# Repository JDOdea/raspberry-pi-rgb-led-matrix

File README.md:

Controlling RGB LED display with Raspberry Pi GPIO
==================================================

A recreated and modified library for controlling 64x64, 32x32, or 16x32 RGB LED panels using a Raspberry Pi. Can support PWM up to 11Bit per channel, providing true 24bpp color with CIE1931 profile.
Original repo can be found [here](https://github.com/hzeller/rpi-rgb-led-matrix).

Supports 3 chains with many panels each on a regular Pi, as per the original repo's README.
Raspberry Pi 2 or 3 can chain 12 panels in that chain (36 panels total), with 96-ish panels (32 chain length) being potentially possible.
Fewer colors or so-called 'outdoor panels' can control even more, faster.

Overview
--------
The RGB LED matrix panels can be bought at [Sparkfun][sparkfun], [AdaFruit][ada] or eBay and Aliexpress. If located in China, try to get directly from some manufacturer, Taobao or Alibaba.

The `RGBMatrix` class in `include/led-matrix.h` is what controls these.
Go to [utils/directory for some ready-made tools](./utils) to get started using the library, or the [examples-api-use/](./examples-api-use/) directory if you want to get started programming your own utils.

Raspberry Pi up to 4 supported
------------------------------

This library supports the old Raspberry Pi's Version 1 with 26 pin header and also the B+ models, the Pi Zero, Raspberry Pi 2 and 3 with 40 pins, as well as the Compute Modules which have 44 GPIOs.

The Raspberry Pi 5 still needs some research into the vastly changed peripherals and is not yet supported. See https://github.com/hzeller/rpi-rgb-led-matrix/issues/1603#issuecomment-2624713250 and https://github.com/adafruit/Adafruit_Blinka_Raspberry_Pi5_Piomatter

The 26 pin models can drive one chain of RGB panels, the 40 pin models **up to three** chains in parallel (each chain 12 or more panels long). The Compute Module can drive **up to 6 chains in parallel**. The Raspberry Pi 2 and 3 are faster and generally preferred to the older models (and the Pi Zero). With the faster models, the panels sometimes can't keep up with the speed; check out this [troubleshooting section](#troubleshooting) for what to do.

A lightweight, non-GUI, distribution such as [DietPi] is recommended. [Raspbian Lite][raspbian-lite] is a bit easier to get started with and is a good second choice.

Types of Displays
-----------------
There are various types of displays that come all with the same Hub75 connector. They vary in the way the multiplexing is happening so this library supports options to choose that.
All these are configured by flags (or, programmatically, in an [Options struct](include/led-matrix.h#L57)).

If you have a 64x32 display, you need to supply the flags `--led-cols=64 --led-rows=32` for instance.

Depending on the Matrix, there are various configuration options that you might need to set for it to work. See further below in the README for the [detailed description of these](#changing-parameters-via-command-line-flags). While the `--led-rows` and the `--led-cols` can be derived from simply looking at the panels, the other options might require some experimenting to find the right setting if there is no description provided by the manufacturer of the panel. Going through these options for experiments would typically not do harm, so feel free to experiment to find your setting.

Flag                                | Description
:---------------      | :-----------------
`--led-cols`          | Columns in the LED matrix, the 'width'.
`--led-rows`          | Rows in the LED matrix, the 'height'.
`--led-multiplexing`  | In particular bright outdoor panels with small multiplex ratios require this. Often an indicator: if there are fewer address lines than expected: ABC (instead of ABCD) for 32 high panels and ABCD (instead of ABCDE) for 64 high panels.
`--led-row-addr-type` | Adressing of rows; in particular panels with only AB address lines might indicate that this is needed.
`--led-panel-type`    | Chipset of the panel. In particular if it doesn't light up at all, you might need to play with this option because it indicates that the panel requires a particular initialization sequence.

Panels can be chained by connecting the output of one panel to the input of the next panel. You can chain quite a few together, but the refresh rate will reduce with longer chains.

The 64x64 matrixes typically come in two kinds: with 5 address lines (A, B, C, D, E), or (A, B); the latter needs a `--led-row-addr-type=1` parameter. So-called 'outdoor panels' are typically brighter and allow for faster refresh-rate for the same size, but do some multiplexing internally of which there are a few types out there; they can be chosen with the `--led-multiplexing` parameter.

There are some panels that have a different chip-set that the default HUB75. These require some initialization sequence. The current supported types are `--led-panel-type=FM6126A` and `--led-panel-type=FM6127`.
Generally, the higher scan-rate (e.g.1:8), a.k.a. outdoor panels generally allow faster refresh rate, but you might need to figure out the multiplexing mapping if one of the three provided does not work.

Some 32x16 outdoor matrixes with 1:4 scan(e.g. [Quangli Q10(1/4) or X10(1/4)](http://qiangliled.com/products-63.html)) have 4 address line (A, B, C, D). For such matrices is necessary to use the `--led-row-addr-type=2` parameter. Also the matrix Quangli Q10(1/4) has "Z"-stripe pixel mapping and in this case, you'd use two parameters at the same time: `--led-row-addr-type=2 --led-multiplexing=4`.

------------
This documentation is split into parts that help you through the process:

    1. [**Wire up the matrix to your Pi**](./wiring.md). This document describes what goes where. You might also be interested in [breakout boards](./adapter) for that. If you have an [Adafruit HAT] or [Adafruit Bonnet], you can choose that with a command line option [described below](#if-you-have-an-adafruit-hat-or-bonnet)
    2. Run a demo. You find that in the [examples-api-use/](./examples-api-use/#running-some-demos) directory:
```
make -C examples-api-use
sudo examples-api-use/demo -D0
```
    3. Use the utilities. The [utils](./utils/) directory has some ready-made useful utilities to show content. [Go there](./utils/) to see how to compile and run these.
    4. Write your own proframs using the Matrix in C++ or one of the bindings such as Python or C#.

### Wiring / Boards

Please see the [Adapter Boards or Self Wiring](./adapter).

Summary:
- Yes you can self wire without level shifters and it will work most of the time, but if you're not in a hurry, get a board
- [This article](https://www.electrodragon.com/product/rgb-matrix-panel-drive-board-for-raspberry-pi-v2/) **is the recommended solution with 3 channels and level shifters.** You can't go wrong there, but expect a bit of shipping time.
- If shipping time is crucial and you don't want to wire your own, Adafruit sells a single channel board (the electrodragon one is 3 channels), but note that its wiring is non-standard and requires a special compile option or command line argument: https://www.adafruit.com/product/3211

### Utilities

The [utils directory](./utils/) is meant for ready utilities to show images or animated gifs or videos. Read the [README](./utils/README.md) for instructions how to compile.

### API

The library comes as an API that you can use for your own utilities and use-cases.

    * The native library is a C++ library (see [include/](./include/)). Example uses you find in the [examples-api-use/](./examples-api-use/) directory.
    * If you prefer to program in C, there is also a [C API](./include/led-matrix-c.h).
    * In the [python](./bindings/python) subdirectory, you'll find a Python API including a couple of [examples](./bindings/python/samples) to get started.

### Changing parameters via command-line flags

For the programs in this distribution and also automatically in your programs using this library, there are a lot of parameters provided as command line flags so that you don't have to re-compile your programs to tweak them. Some might need to be changed for your particular kind of panel.

Here is a small run-down of what these command-line flags do and when you'd like to change them.

First: if you have a different wiring than described in [wiring](./wiring.md), for instance if you have an Adafruit HAT/Bonnet, you can choose these here:

```
--led-gpio-mapping=<gpio-mapping>: Name of GPIO mapping used. Default "regular"
```

This can have values such as
    - `--led-gpio-mapping=regular`          The standard mapping of this library, described in the [wiring](./wiring.md) page.
    - `--led-gpio-mapping=adafruit-hat`     The Adafruit HAT/Bonnet that uses this library, or
    - `--led-gpio-mapping=adafruit-hat-pwm` Adafruit HAT with the anti-flicker hardware mod [described below](#improving-flicker).
    - `--led-gpio-mapping=compute-module`   Additional 3 parallel chains can be used with the Compute Module.

Learn more about the mappings in the [wiring documentation](wiring.md#alternative-hardware-mappings).

#### GPIO speed

```
--led-slowdown-gpio=<0..4>: Slowdown GPIO. Needed for faster Pis and/or slower panels (Default: 1).
```

The Raspberry Pi starting with Pi2 are putting out data too fast for almost all LED panels seen. In this case, you want to slow down writing to GPIO. Zero for this parameter means 'no slowdown'.

The default 1 (one) typically works fine, but often you have to go even further by setting it to 2 (two). If you have a Raspberry Pi with a slower processor (Model A, A+, B+, Zero), then a value of 0 (zero) might work and is desirable.

A Raspberry Pi 3 or Pi4 might even need higher values for the panels to be happy.

#### Panel Connection
The next most important flags describe the type and number of displays connected:

```
--led-rows=<rows>           : Panel rows. Typically 8, 16, 32, or 64. (Default: 32).
--led-cols=<cols>           : Panel columns. Typically 32 or 64. (Default: 32).
--led-chain=<chained>       : Number of daisy-chained panels. (Default: 1).
--led-parallel=<parallel>   : For A/B+ models of RPi2,3b: parallel chains. range=1..3 (Default: 1, 6 for Compute Module).
```

These are the most important ones: here you choose how many panels you have connected and how many rows are in each panel. Panels can be chained (each panel has an input and output connector, see the [wiring documentation](wiring.md#chains)) -- the `--led-chain` flag tells the library how many panels are chained together. The newer Raspberry Pis allow to connect multiple chains in parallel, the `--led-parallel` flag tells it how many there are.

This illustrates what each of these parameters mean:

##### Panel Type

Typically, panels should just work out of the box, but some panels use a different chip-set that requires some initialization. If you don't see any output on your panel, try setting:

```
--led-panel-type=FM6126A
```

Some panels have the FM6127 chip, which is also an option.

##### Multiplexing
If you have some 'outdoor' panels or panels with different multiplexing, the following will be useful:

```
--led-multiplexing=<0..17> : Mux type: 0=direct; 1=Stripe; 2=Checkered...
```

The outdoor panels have different multiplexing which allows them to be faster and brighter, but by default their output looks jumbled up. They require some pixel-mapping of which there are a few types you can try and hopefully one of them works for your panel; The default=0 is no mapping ('standard' panels), while 1, 2, ... are different mappings to try with. If your panel has a different mapping, you find everything you need to implement one in [lib/multiplex-mappers.cc](lib/multiplex-mappers.cc).

Note that you have to set the `--led-rows` and `--led-cols` to the rows and columns that are physically on each chained panel so that the multiplexing option can work properly. For instance a `32x16` panel with `1:4` multiplexing would be controlled with `--led-rows=16 --led-cols=32 --led-multiplexing=1` (or whatever multiplexing type your panel is, so it can also be `--led-multiplexing=2` ...).

For `64x32` panels with `1:8` multiplexing, this would typically be `--led-rows=32 --led-cols=64 --led-multiplexing=1`; however, there are some panels that internally behave like two chained panels, so then you'd use `--led-rows=32 --led-cols=32 --led-chain=2 --led-multiplexing=1`;

```
--led-row-addr-type=<0..4>: 0 = default; 1 = AB-addressed panels; 2 = direct row select; 3 = ABC-addressed panels; 4 = ABC Shift + DE direct (Default: 0).
```

This option is useful for certain 64x64 or 32x16 panels. For 64x64 panels that only have an `A` and `B` address line, you'd use `--led-row-addr-type=1`. This is only tested with one panel so far.

For 32x16 outdoor panels that have 4 address lines (A, B, C, D), it is necessary to use `--led-row-addr-type=2`.

#### Panel Arrangement

```
--led-pixel-mapper  : Semicolon-separated list of pixel-mappers to arrange pixels.
```

Optional params after a colon e.g. "U-mapper;Rotate:90"

Available | Parameter after colon| Example
----------|----------------------|----------
Mirror    | `H` or `V` for horizontal/vertical mirror. | `Mirror:H`
Rotate    | Degrees.                                   | `Rotate:90`
U-mapper  | -

Mapping the logical layout of your boards to your physical arrangement. See
more in [Remapping coordinates](./examples-api-use#remapping-coordinates).

#### Misc Options

```
--led-brightness=<percent>: Brightness in percent (Default: 100).
```

Self explanatory.

```
--led-pwm-bits=<1..11>    : PWM bits (Default: 11).
```

The LEDs can only be switched on or off, so the shaded brightness perception is achieved via PWM (Pulse Width Modulation). In order to get a good 8bit per color resolution (24bit RGB), the 11 bits default per color are good (Why? Because our eyes are actually perceiving brightness logarithmically, so we need a lot more physical resolution to get 24bit sRGB).

With this flag, you can change how many bits it should use for this; lowering it means the lower bits (=more subtle color nuances) are omitted. Typically you might be mostly interested in the extremes: 1bit for situations that only require 8 colors (e.g. for high contrast text displays) or 11bit for everything else (e.g. showing images or videos). Why would you bother at all? Lower number of bits use slightly less CPU and result in a higher refresh rate.

```
--led-show-refresh        : Show refresh rate.
```

This shows the current refresh rate of the LED panel, the time to refresh a full picture. Typically, you want this number to be pretty high, because the human eye is pretty sensitive to flicker. Depending on the settings, the refresh rate with this library is typically in the hundreds of Hertz, but can drop low with very long chains. Humans have different levels of perceiving flicker - some are fine with 100Hz refresh, others need 250Hz. So if you are curious, this gives you the number (shown on the terminal).

The refresh rate depends on a number of different factors, from `--led-rows` and `--led-chain` to `--led-pwm-bits`, `--led-pwm-lsb-nanoseconds`, and `--led-pwm-dither-bits`. If you are tweaking these parameters, showing the refresh rate can be a useful tool.

```
--led-limit-refresh=<Hz>  : Limit refresh rate to this frequency in Hz. Useful to keep a
                            constant refresh rate on loaded system. 0=no limit. Default: 0
```

This allows to limit the refresh rate to a particular frequency to approach a fixed refresh rate.

This can be used to mitigate some situations in which you have a faint flicker, which can happen due to hardware events (network access) or other situations such as other IO or heavy memory access by other processes. Also when you see wildly changing refresh frequencies with `--led-show-refresh`.

You trade a slightly slower refresh rate and display brightness for less visible flicker situations.

For this to calibrate, run your program for a while with --led-show-refresh and watch the line that shows the current refresh rate and minimum refresh rate observed. So wait a while until that value doesn't change anymore (e.g. a minute, so that you catch tasks that happen once a minute, such as ntp updated). Use this as a guidance what value to choose with `--led-limit-refresh`.

The refresh rate will now be adapted to always reach this value between frames, so faster refreshes will be slowed down, but the occasional delayed frame will fit into the time-window as well, thus reducing visible brightness fluctuations.

You can play with value a little and reduce until you find a good balance between refresh rate and flicker suppression.

Use this also if you want to have a stable baseline refresh rate when using the vsync-multiple flag `-V` in the [led-image-viewer] or [video-viewer] utility programs.

```
--led-no-busy-waiting     : Don't use busy waiting when limiting refresh rate.
```

This allows to switch from busy waiting to sleep waiting when limiting the refresh rate (`--led-limit-refresh`).

By default, refresh rate limiting uses busy waiting, which is CPU intensive but gives most accurate timings. This is fine for multi-core boards.

On single core boards (e.g. Raspberry Pi Zero) busy waiting makes the system unresponsive for other/background tasks. There, sleep waiting improves the system's responsiveness at the cost of slightly less accurate timings.

```
--led-scan-mode=<0..1>    : 0 = progressive; 1 = interlaced (Default: 0).
```

This switches from progressive scan and interlaced scan. The latter might look to be a little nicer when you have a very low refresh rate, but typically it is more annoying due to the comb-effect.

```
--led-pwm-lsb-nanoseconds : PWM Nanoseconds for LSB (Default: 130)
```

This allows to change the base time-unit for the on-time in the lowest significant bit in nanoseconds. Lower values will allow higher frame-rate, but will also negatively impact quality in some panels (less accurate color or more ghosting).

Good values for full-color display (PWM=11) are somewhere between 100 and 300.

If you use reduced bit color (e.g. PWM=1) and have sharp contrast applications, then higher values might be good to minimize ghosting.

How should you decide? Just leave the default if things are running fine. However, some panels have trouble with sharp contrasts and short pulses that results in ghosting. It is particularly apparent in situations such as bright text on black background. In these cases, increase the value until you don't see the ghosting anymore.

The following example shows how this might look like:

Ghosting with low --led-pwm-lsb-nanoseconds  | No ghosting after tweaking
---------------------------------------------|------------------------------
                   |

If you tweak this value, watch the framerate (`--led-show-refresh`) while playing
with this number.

```
--led-pwm-dither-bits   : Time dithering of lower bits (Default: 0)
```

The lower bits can be time dithered, i.e. their brightness contribution is achieved by only showing them some frames (this is possible because the PWM is implemented as binary code modulation). This will allow higher refresh rate (or same refresh rate with increased `--led-pwm-lsb-nanoseconds`). The disadvantage could be slightly lower brightness, in particular for longer chains, and higher CPU use. CPU use is not of concern for Raspberry Pi 2 or 3 (as we run on a dedicated core anyway) but probably for Raspberry Pi 1 or Zero. Default: no dithering; if you have a Pi 3 and struggle with low frame-rate due to high multiplexing panels (1:16 or 1:32) or long chains, it might be worthwhile to try.

```
--led-no-hardware-pulse   : Don't use hardware pin-pulse generation.
```

This library uses a hardware subsystem that also is used by the sound. You can't use them together. If your panel doesn't work, this might be a good start to debug if it has something to do with the sound subsystem (see Troubleshooting section). This is really only recommended for debugging; typically you actually want the hardware pulses as it results in a much more stable picture. 

```
--led-no-drop-privs       : Don't drop privileges from 'root' after initializing the hardware.
```

You need to start programs as root, as it needs to access some low-level hardware at initialization time. After that, it is typically not desirable to stay in this role, so the library then drops the privileges.

This flag allows to switch off this behavior so that you can stay root. Not recommended unless you have a specific reason for it (e.g. you need root to access other hardware or you do the privilege dropping yourself).

```
--led-daemon              : Make the process run in the background as daemon.
```

If this is set, the program puts itself into the background (running as 'daemon'). You might want this if started from an init script at boot-time.

```
--led-inverse             : Switch if your matrix has inverse colors on.
--led-rgb-sequence        : Switch if your matrix has led colors swapped (Default: "RGB")
```

These are if you have a different kind of LED panel in which the logic of the color bits is reversed (`--led-inverse`) or where the Red, Green, and Blue LEDs are mixed up (`--led-rgb-sequence`). You know it when you see it.

Troubleshooting
---------------
Here are some tips in case things don't work as expected.

### Use minimal Raspbian distribution
In general, run a minimal configuration on your Pi.

    * Do not use a graphical user interface (even though the Raspberry Pi foundation makes you believe that you can. Using a Pi with a GUI is an extremely slow use of an otherwise perfectly good embedded device). Always operate your Raspberry Pi [headless].

    * Switch off on-board sound (`dtparam=audio=off` in `/boot/config.txt` pre-bookworm) (`dtparam=audio=off` in `/boot/firmware/config.txt` post-bookworm). External USB sound adapters work, and are much better quality anywar, so that is recommended if you happen to need sound. The on-board sound uses a timing circuit that the RGB-Matrix needs (it seems in some distributions, such as arch-linux, this is not enough and you need to explicitly blacklist the snd_bcm2835 module).

    * Don't run anything that messes in parallel with the GPIO pins, e.g. PiGPIO library/daemon or devices that use the i2c or 1-wire interface if they are on the same pins you need for the panel.

    * There are also reports that on some Pis, the one-wire protocol is enabled (w1-gpio). This will also not work (disable by removing `dtoverlay=w1-gpio` in `/boot/config.txt` pre-bookworm or in `/boot/firmware/config.txt` post-bookworm; or using `raspi-config`, Interface Options -> 1-Wire)

    * If you see some regular flickering, make sure that there is no other process running on the system that could cause that. For isntance, it is known that merely running `top` creates a faint flicker every second it updates. Or a regular ntp run can also cause flicker once a minute (switch off with `sudo timedatect1 set-ntp false`). Maybe instead you might want to run ntp at system start-up but then not regularly updating. There might be other things running regularly you don't need; consider a `sudo systemct1 stop cron` for instance. To address some irregular flicker, consider the [`--led-limit-refresh`](#misc-options) option.

    * There are probably other processes that are running that you don't need.
    ```
    sudo apt-get remove bluez bluez-firmware pi-bluetooth triggerhappy pigpio
    ```
    Take a close look at your systemd (`systemctl`) and see if there are other things running you don't need. In general, this is why starting with a minimal installation is a good idea; there is simply less cruft that you have to disable.

    * More recent versions of Raspbian Lite result in some faint brightness fluctuations of the displays and it isn't quite clear why.

The default install of **[Raspbian Lite][raspbian-lite]** or **[DietPi]** seem to be good starting points, as they have a reasonably minimal configuration to begin with. Raspbian Lite is not as lite as it used to be.

### Bad interaction with Sound
If sound is enabled on your Pi, this will not work together with the LED matrix, as both need the same internal hardware sub-system (a first test to see if you are affected is to run the program with `--led-no-hardware-pulse` and see if things work fine then).

If you run `lsmod` and see the `snd_bcm2835` module, this could be causing trouble. (The library actually exits if it finds this module to be loaded).

In that case, you should create a kernel module blacklist file like the following on your system and update your initramfs:

```
cat <<EOF | sudo tee /etc/modprobe.d/blacklist-rgb-matrix.conf
blacklist snd_bcm2835
EOF

sudo update-initramfs -u
```

Reboot and confirm that the module is not loaded.

### I have followed some tutorial on the Internet and it doesn't work

If you use this library, please read the documentation provided _here_, not on some other website. Most important to get started with is the [wiring guide](./wiring.md). 

### I have a Pi1 Revision1 and top part of Panel doesn't show green

Use `--led-gpio-mapping=regular-pi1`

### Logic level voltage not sufficient
Some panels don't interpret the 3.3V logic level well, or the RPi output drivers have trouble driving longer cables, in particular with faster Raspberry Pis Version 2. This results in artifacts like randomly showing up pixels, color fringes, or parts of the panel showing 'static'.

If you encounter this, try these things:

   - Make sure to have as short as possible flat-cables connecting your
     Raspberry Pi with the LED panel.

   - In particular if the chips close to the input of the LED panel
     read 74HC245 instead of 74HCT245 or 74AHCT245, then this board will not
     work properly with 3.3V inputs coming from the Pi.
     Use an [adapter board](./adapter/active-3) with a bus-driver that acts as
     level shifter between 3.3V and 5V.
     (In any case, it is always a good idea to use the level shifters).

   - A temporary hack to make HC245 inputs work with the 3.3V levels is to
     supply only like 4V to the LED panel. But the colors will be off, so not
     really useable as long-term solution.

   - If you can't implement the above things, or still have problems, you can
     slow down the GPIO writing a bit. This will of course reduce the
     frame-rate, so it comes at a cost.

For GPIO slow-down, add the flag `--led-slowdown-gpio=2` to the invocation of the binary.

If you have an Adafruit HAT or Bonnet
---------------------------

Generally, if you want to connect RGB panels via an adapter instead of hand-wiring, I suggest to build one of the adapters whose open-hardware files you find in the [adapter/](./adapter) subdirectory. It is a fun solder exercise with large surface mount components.

However, Adafruit [offers an adapter][adafruit-hat] which is already ready-made, but it only allows for a single chain. If the ready-made vs. single-chain tradeoff is worthwhile, then you might go for that.

### Switch the Pinout

The Adafruit HAT/Bonnet uses this library but a modified pinout to support other features on the HAT. You can choose the Adafruit pinout with a command line flag.

Just pass the option `--led-gpio-mapping=adafruit-hat`. This works on the C++ and Python examples.

### Improving flicker

To improve flicker, we need to do a very simple hardware modification: solder a wire between GPIO 4 and 18 as shown in the following picture (click to enlarge):

Then, start your programs with `--led-gpio-mapping=adafruit-hat-pwm`.

Now you should have less visible flicker. This essentially switches on the hardware pulses feature for the Adafruit HAT/Bonner.

### 64x64 with E-line on Adafruit HAT/Bonnet
There are LED panels that have 64x64 LEDs packed, but they need 5 address lines, which is 1:32 multiplexing (they have an `E` address-line). The first generation of the Adafruit HAT/Bonnet was not prepared for this, but it can be done with another hardware mod. Beginning October 2018, Adafruit began selling an updated version of the HAT that supports 64x64 panels simply by bridging two pads on the PCB with solder.

You can identify which HAT you have by looking for the **Address E** pads, circled here:

### New Adagruit RGB Matrix Hat (with Address E pads)

Look for the Address E pads located between the HUB75 connector and Pi camera cutout.

Mult a blob of solder between the center "E" pad and the "8" pad just above it (for 64x64 matrices in the Adafruit shop)…*_or_* the "16" pad below (rare, for some third-party 64x64 matrices_check datasheet).

### Old Adafruit HAT/Bonnet (without)

It is a little more advanced hack, so it is only really for people who are comfortable with this kind of thing.
First, you have to figure out which is the input of the E-Line on your matrix (they seem to be either on Pin 4 or Pin 8 of the IDC connector). You need to disconnect that Pin from the ground plane (e.g. with an Exacto knife) and connect GPIO 24 to it. The following images illustrate the case for IDC Pin 4.

If the direct connection does not work, you need to send it through a free level converter of the Adafruit HAT/Bonnet. Since all unused inputs are grounded with traces under the chip, this involves lifting a leg from the HCT245 (figure out a free bus driver from the schematic). If all of the above makes sense to you, you have the ability to do it.

It might be more convenient at this point to consider the [Active3 adapter](./adapter/active-3) that has that already covered.

Running as root
---------------
The library requires access to hardware registers to control the LED matrix and to create accurate timings. These hardware accesses require to run as root user.

For security reasons, it is usually not a good idea to run an application as root entirely, so this library makes sure to drop privileges immediately after the hardware is initialized.

You can switch off the privilege dropping with the [`--led-no-drop-privs`](#user-content-no-drop-priv) flag, or, if you do this programmatically, choose the configuration in the ['RuntimeOptions struct'](https://github.com/hzeller/rpi-rgb-led-matrix/blob/master/include/led-matrix.h#L401).

Note, you _could_ run as non-root, which will use `/dev/gpiomem` to at least write to GPIO, however the precise timing hardware registers are not accessible. This will result in flicker and color degradation. Starting as non-root is not recommended.

CPU use
-------

These displays need to be updated constantly to show an image with PWMed LEDs. This is dependent on the length of the chain: for each chain element, about 1'000'000 write operations have to happen every second! (chain_length * 32 pixel long * 16 rows * 11 bit planes * 180 Hz refresh rate).

We can't use hardware support for writing these as DMA is too slow, thus the constant CPU use on an RPi is roughly 30-40% of one core. Keep that in mind if you plan to run other things on this computer (This is less noticable on Raspberry Pi, Version 2 or 3 that has more cores).

Also, the output quality is susceptible to other heavy tasks running on that computer - there might be changes in the overall brightness when this affects the refresh rate.

If you have a loaded system and one of the newer Pis with 4 cores, you can reserve one core just for the refresh of the display. Add:

```
isolcpus=3
```

to the end of the line in `/boot/cmdline.txt` (pre-bookworm) or `boot/firmware/cmdline.txt` (post-bookworm). It needs to be in the same line as the existing arguments -- no newline. This will use the last core only to refresh the display then, but it also means that no other process can utilize it then.

Performance improvements and limits
-----------------------------------
Regardless of which driving hardware you use, ultimately you can only push pixels so fast to a string of panels before you get flickering due to too low a refresh rate (less than 80-100Hz), or before you refresh the panel lines too fast and they appear too dim because each line is not displayed long enough before it is turned off.

Basic performance tips:
- Use --led-show-refresh to see the refresh rate while you try parameters
- use an active-3 board with led-parallel=3
- led-pwm-dither-bits=1 gives you a speed boost but less brightness
- led-pwm-lsb-nanoseconds=50 also gives you a speed boost but less brightness
- led-pwm-bits=7 or even lower decrease color depth but increases refresh speed
- AB panels and other panels with that use values of led-multiplexing bigger than 0,
will also go faster, although as you tune more options given above, their advantage will decrease.
- 32x16 ABC panels are faster than ABCD which are faster than ABCDE, which are faster than 128x64 ABC panels
(which do use 5 address lines, but over only 3 wires)
- Use at least an rPi3 (rPi4 is still slightly faster but may need --led-slowdown-gpio=2)

Maximum resolutions reasonably achievable:
A general rule of thumb is that running 16K pixels (128x128 or otherwise) on a single chain is already pushing limits and you will have to make tradeoffs in visual quality. 32K pixels (like 128x256) is definitely pushing things and you'll have to make tradeoffs in visual quality. 32K pixels (like 128x256) is definitely pushing things and you'll get 100Hz or less depending on the performance options you choose.
This puts the maximum reasonable resolution around 100K pixels (like 384x256) for 3 chains.
You can see more examples and video capture of speed on [Marc MERLIN's page 'RGB Panels, from 192x80, to 384x192, to 384x256 and maybe not much beyond'](http://marc.merlins.org/perso/arduino/post_2020-03-13_RGB-Panels_-from-192x80_-to-384x192_-to-384x256-and-maybe-not-much-beyond.html)
If your refresh rate is below 300Hz, expect likely black bars when taking cell phone pictures.
A real camera with shutter speed lowered accordingly will get around this.

Ultimately, you should not expect to go past 64K pixels using 3 chains without significant quality tradeoffs. If you need bigger displays, you should use multiple boards and synchronize the output.

Limitations
-----------
If you are using the Adafruit HAT/Bonnet in the default configuration, then we can't make use of the PWM hardware (which only outputs to a particular pin), so you'll see random brightness glitches. I strongly suggest to do the aforementioned hardware mod.

The system needs constant CPU to update the display. Using the DMA controller was considered but after experiments, was dropped due to slow speed.

There is an upper limit in how fast the GPIO pins can be controlled, which limits the frame-rate. Raspberry Pi 2's and newer are generally faster.

Even with everything in place, you might see faint brightness fluctuations in particular if there is something going on in the network or in a terminal on the Pi; this could probably be mitigated with some more real-time kernel for the Pi; maybe there are also hardware limitations (memory bus contention?).

To address the brightness fluctuations, you might experiment with the `FIXED_FRAME_MICROSECONDS` compile time option in [lib/Makefile](lib/MakeFile) that has instructions on how to set it up.

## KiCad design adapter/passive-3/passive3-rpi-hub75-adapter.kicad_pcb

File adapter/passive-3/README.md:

Adapter PCB to support up to 3 panel chains
===========================================

   * This is a passive board. It is simple, but the logic level will be out of
     spec for the LED matrix (3.3V vs. 5V) which might or might not work.
     Driving long cables with the GPIO pins is also not a good idea.
   * You typically want to consider using the [active board](../active-3).
   * Works for Matrix up to 1:16 multiplexing (32 rows). For 1:32 multiplexing,
     you want to use the [active board](../active-3). You can of also hack
     this board as [suggested in this bugtracker entry](https://github.com/hzeller/rpi-rgb-led-matrix/issues/360#issuecomment-321104348) to make it work with
     64x64 boards.
   * Only really advisable, if the LED panels have 74HCT245 (as opposed to just
     74HC245) in their input stage, because then they can deal properly with
     the 3.3V logic levels coming from the Pi.
   * Supports up to three panel chains for newer plus models and
     Raspberry Pi 2/3 that have 40 GPIO pins.
   * Open source KiCAD PCB EDA format.
   * (not very pretty layout, was just lazy and let the auto-router do it).
   * The FAB files are provided as [passive3-rpi-hub75-adapter-fab.zip](./passive3-rpi-hub75-adapter-fab.zip)

This board is [shared on OSH Park][osh-passive3] (not affiliated).

![Preview][rendering]

[rendering]: ../../img/passive3-pcb.png
[osh-passive3]: https://oshpark.com/shared_projects/FNAtZUsP

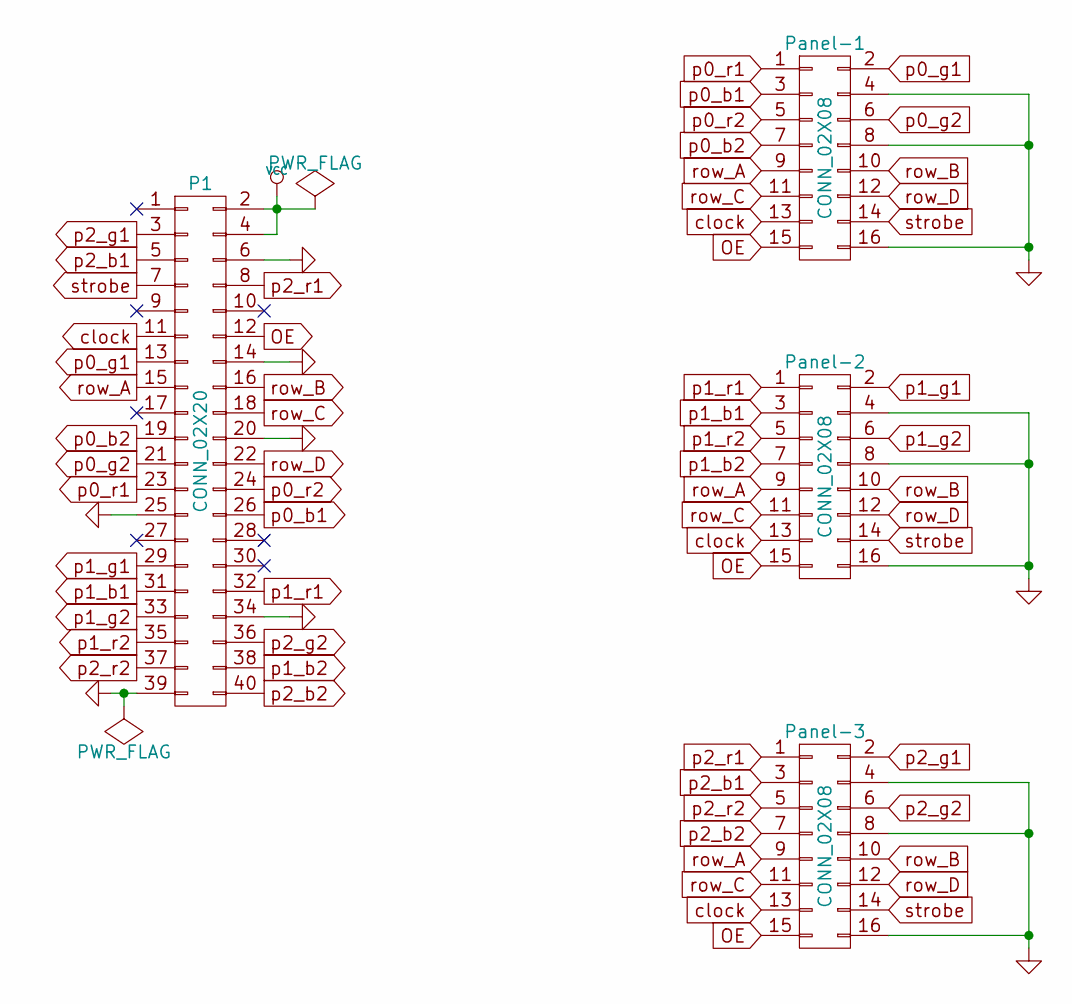
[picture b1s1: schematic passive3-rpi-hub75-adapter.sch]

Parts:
P1: CONN_02X20; Pin_Header_Straight_2x20
Panel-1, Panel-2, Panel-3: CONN_02X08; Pin_Header_Straight_2x08

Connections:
GND: P1.6, P1.14, P1.20, P1.25, P1.34, P1.39, Panel-1.4, Panel-1.8, Panel-1.16, Panel-2.4, Panel-2.8, Panel-2.16, Panel-3.4, Panel-3.8, Panel-3.16
OE: P1.12, Panel-1.15, Panel-2.15, Panel-3.15
VCC: P1.2, P1.4
clock: P1.11, Panel-1.13, Panel-2.13, Panel-3.13
p0_b1: P1.26, Panel-1.3
p0_b2: P1.19, Panel-1.7
p0_g1: P1.13, Panel-1.2
p0_g2: P1.21, Panel-1.6
p0_r1: P1.23, Panel-1.1
p0_r2: P1.24, Panel-1.5
p1_b1: P1.31, Panel-2.3
p1_b2: P1.38, Panel-2.7
p1_g1: P1.29, Panel-2.2
p1_g2: P1.33, Panel-2.6
p1_r1: P1.32, Panel-2.1
p1_r2: P1.35, Panel-2.5
p2_b1: P1.5, Panel-3.3
p2_b2: P1.40, Panel-3.7
p2_g1: P1.3, Panel-3.2
p2_g2: P1.36, Panel-3.6
p2_r1: P1.8, Panel-3.1
p2_r2: P1.37, Panel-3.5
row_A: P1.15, Panel-1.9, Panel-2.9, Panel-3.9
row_B: P1.16, Panel-1.10, Panel-2.10, Panel-3.10
row_C: P1.18, Panel-1.11, Panel-2.11, Panel-3.11
row_D: P1.22, Panel-1.12, Panel-2.12, Panel-3.12
strobe: P1.7, Panel-1.14, Panel-2.14, Panel-3.14

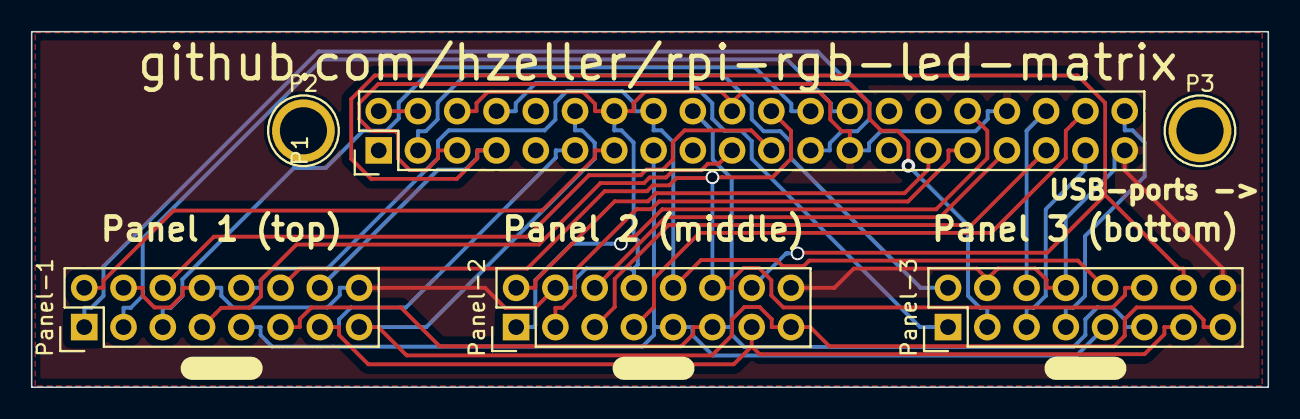
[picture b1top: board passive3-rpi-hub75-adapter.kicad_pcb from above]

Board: 2 copper layers, 80.0 x 23.0 mm, 6 parts (0 on the bottom side), 27 nets.

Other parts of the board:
P2, P3: CONN_01X01; 1pin

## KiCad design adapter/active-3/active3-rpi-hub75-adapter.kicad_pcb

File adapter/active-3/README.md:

Adapter PCB to support up to 3 panel chains
===========================================

   * Supports up to three panel chains for newer plus models and
     Raspberry Pi 2 that have 40 GPIO pins.
   * Uses HCT245 to level shift signals from 3.3V to 5V and shield
     the Raspberry Pi GPIOs from overloading.
   * Open source KiCAD PCB EDA format.
   * Optional: Pads to power the Pi with 5V, including optional capacitor footprints.
   * Connector for RxD input (literally the only GPIO pin left) in case you want to
     make your panel controlled with a serial interface (3.3V logic level).
   * Provides a way to choose the pinout for different kinds of 64x64 matrixes.
   * (not very pretty layout, was just lazy and let the auto-router generate the first pass)
   * BOM:
     - 4x 74HCT245 or 74AHCT245 in 20-SOIC, 7.5mm package which should make
     it easy to hand-solder. Make sure to get the variant with the **T**: HC**T** or AHC**T**
     (there are also HC or AHC, don't use these).
     - 4x 100nF ceramic capacitor (0805 package)
     - 1x 10kOhm resistor (0805 package). Not critcial, just a pullup (2.2k .. 15k probably ok).
     - 3x 16pin IDC (=2x8) male receptible to connect the panels.
     - 1x 40pin female connector to connect to the RPi.
     - 1x (optional) 22μF .. 100μF capacitor for 5V rail (either 1206 SMD or
       radial electrolytic with 2.5mm pitch/6.3mm diameter)
   * The Gerber FAB files are provided as [active3-rpi-hub75-adapter-fab.zip](./active3-rpi-hub75-adapter-fab.zip)

The board is also [shared on OSH Park][osh-active3] (not affiliated).

![Preview][rendering]
![Real World][real-world]

Essentially, this is connecting the output pins through level shifting buffers (they
are operated at 5V, but the HCT series chips accept 3.3V input levels from the Pi). The
strobe, OE and clock signals are separately buffered for each connector.

![Schematic][schematic]

## Optional

### Power in

The area on the left has 5V/GND input pads, that allow you to power your Raspberry Pi from
a 5V source ... which you are likely to have as you are powering the LED Matrix. This is often
more convenient than using the USB connector to power the Pi.

If you do that, there are pads to add a capacitor to smooth the supply - two footprints are
provided: C5 and C6 for through-hole or surface mount components. The value is not critical;
I usually use a 22μF/6.3V ceramic capacitor on the C6 pads.

### Choose E-Line for 64x64 panels with 1:32 multiplexing

If you have a 64x64 matrix with 1:32 multiplexing, you need to supply an `E`-address line to it.
While the Address lines `A` to `D` have fixed positions on the Hub75 connector, there
seem to be two different ways to connect the `E` address line: it is either on pin 4 or pin 8
of the connector. So this adapter board provides the flexibility to choose the right pin for
your matrix.

Look at the back of the matrix or the documentation to find out for your specific board where
to connect E.

Once you know that, the jumper area in the bottom left of this adapter board allows to choose
to which pin to connect the E-address line to. The corresponding other pin should be connected
to GND. Simply solder a wire bridge as indicated below (or use a jumper that you can change later).

If you are not using such 64x64 matrix, you can connect both these pins to GND.

Here are the typical configurations:

No 1:32 64x64: to GND    | E-Line on Pin 4   | E-Line on Pin 8|
-------------------------|-------------------|----------------
![][config-default]      |![][config-pin4]   |![][config-pin8]

### Input for serial RxD

If you are not using a 64x64 display that occupies the E-Line, you can use the RxD serial input -
this might come in handy if you are using the display to be controlled by a serial line. Be aware
that the input requires 3.3V level, so if you have a RS232, make sure to first adapt the levels.

[rendering]: ../../img/active3-pcb.png
[config-default]: ../../img/active3-pcb-config-default.png
[config-pin4]: ../../img/active3-pcb-config-pin4.png
[config-pin8]: ../../img/active3-pcb-config-pin8.png
[schematic]: ../../img/active3-schematic.png
[real-world]: ../../img/three-parallel-panels-soic.jpg
[osh-active3]: https://oshpark.com/shared_projects/6xAD1VXr

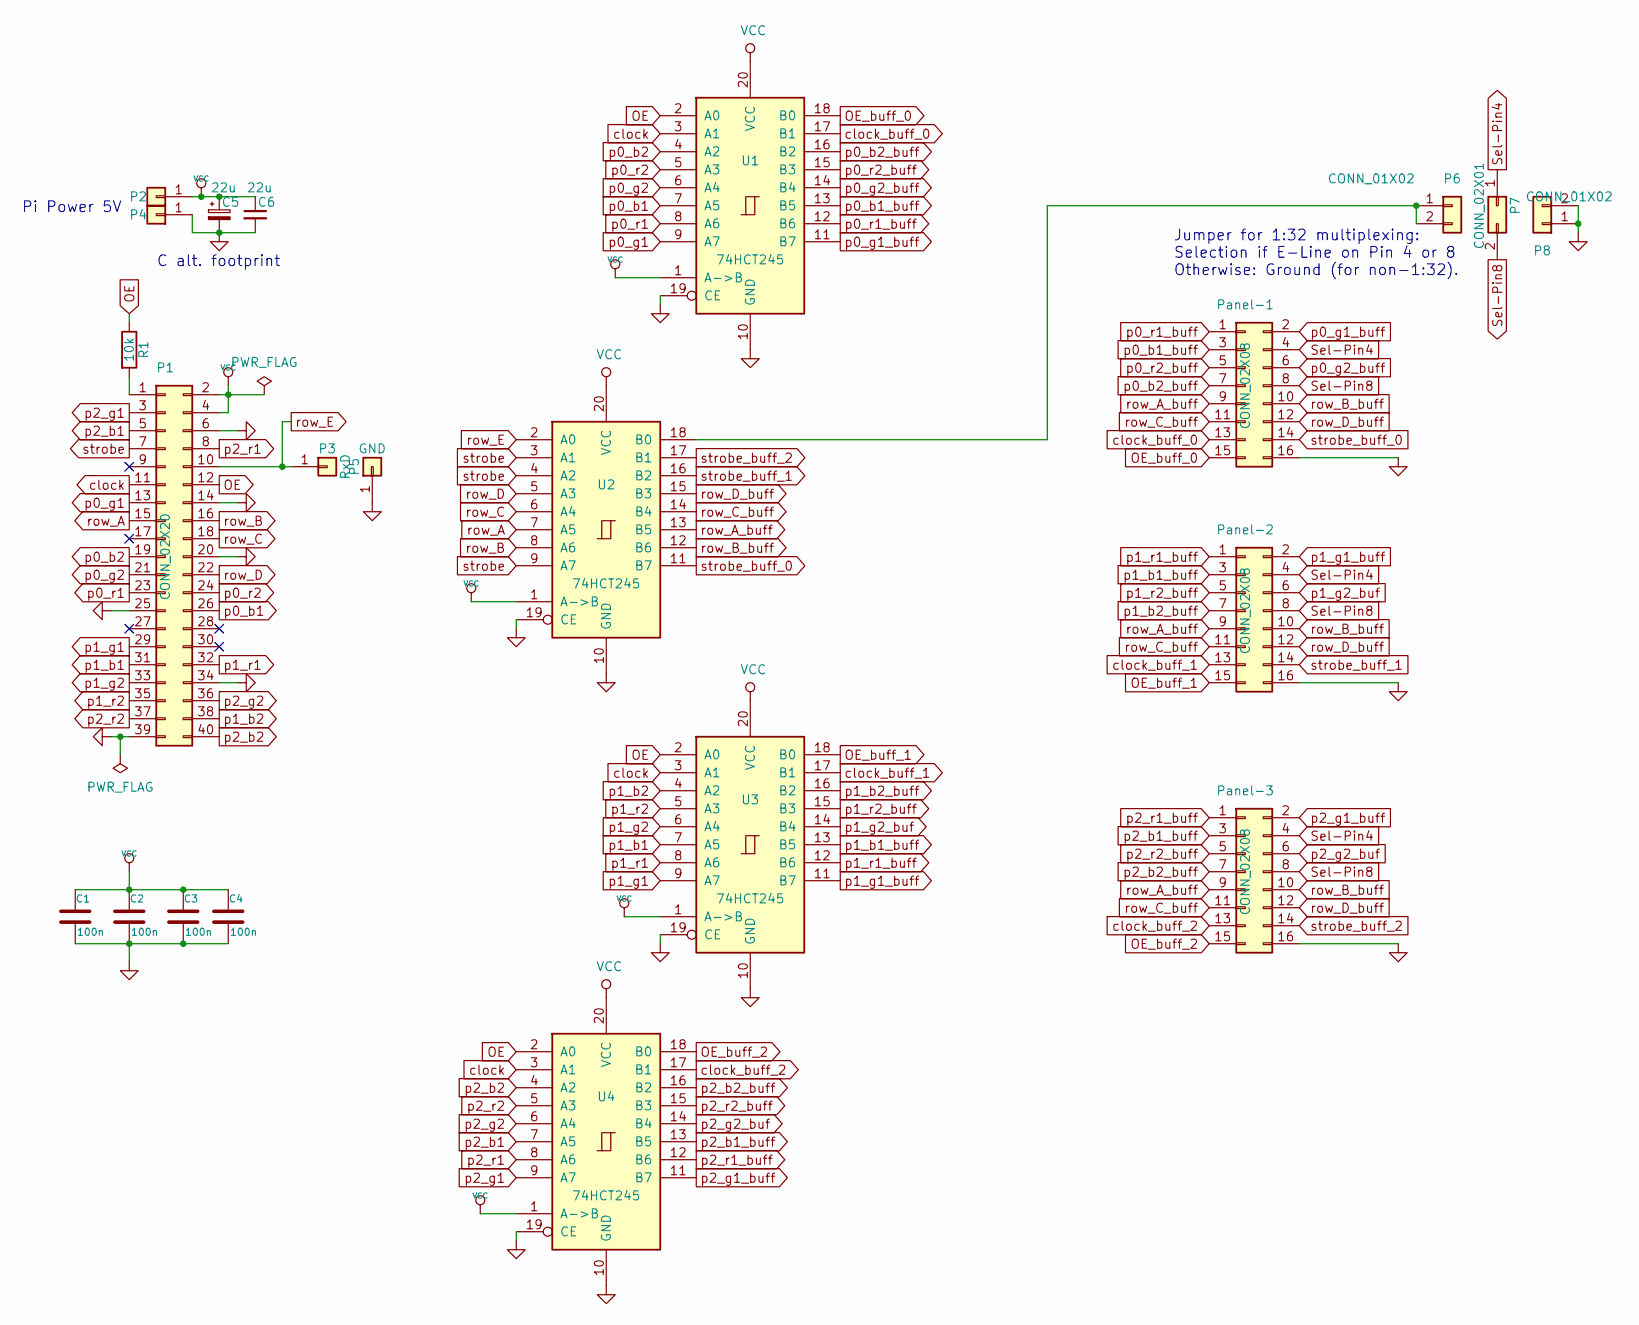
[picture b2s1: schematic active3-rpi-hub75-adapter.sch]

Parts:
C1, C2, C3, C4: 100n; C_0805_2012Metric
C5: 22u; CP_Radial_D6.3mm_P2.50mm
C6: 22u; C_1206_3216Metric
P1: CONN_02X20; Pin_Header_Straight_2x20
P2: +5V; Pin_Header_Straight_1x01
P3: RxD; Pin_Header_Straight_1x01
P4, P5: GND; Pin_Header_Straight_1x01
P6, P8: CONN_01X02; Pin_Header_Straight_1x02
P7: CONN_02X01; Pin_Header_Straight_1x02
Panel-1, Panel-2, Panel-3: CONN_02X08; IDC-Header_2x08_P2.54mm_Vertical
R1: 10k; R_0805_2012Metric
U1, U2, U3, U4: 74HCT245; SOIC-20W_7.5x12.8mm_P1.27mm

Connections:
GND: C1.2, C2.2, C3.2, C4.2, C5.2, C6.2, P1.6, P1.14, P1.20, P1.25, P1.34, P1.39, P4.1, P5.1, P8.1, P8.2, Panel-1.16, Panel-2.16, Panel-3.16, U1.10 (GND), U1.19 (CE), U2.10 (GND), U2.19 (CE), U3.10 (GND), U3.19 (CE), U4.10 (GND), U4.19 (CE)
unnamed: P1.1, R1.2
unnamed: P6.1, P6.2, U2.18 (B0)
OE: P1.12, R1.1, U1.2 (A0), U3.2 (A0), U4.2 (A0)
OE_buff_0: Panel-1.15, U1.18 (B0)
OE_buff_1: Panel-2.15, U3.18 (B0)
OE_buff_2: Panel-3.15, U4.18 (B0)
Sel-Pin4: P7.1, Panel-1.4, Panel-2.4, Panel-3.4
Sel-Pin8: P7.2, Panel-1.8, Panel-2.8, Panel-3.8
VCC: C1.1, C2.1, C3.1, C4.1, C5.1, C6.1, P1.2, P1.4, P2.1, U1.1 (A->B), U1.20 (VCC), U2.1 (A->B), U2.20 (VCC), U3.1 (A->B), U3.20 (VCC), U4.1 (A->B), U4.20 (VCC)
clock: P1.11, U1.3 (A1), U3.3 (A1), U4.3 (A1)
clock_buff_0: Panel-1.13, U1.17 (B1)
clock_buff_1: Panel-2.13, U3.17 (B1)
clock_buff_2: Panel-3.13, U4.17 (B1)
p0_b1: P1.26, U1.7 (A5)
p0_b1_buff: Panel-1.3, U1.13 (B5)
p0_b2: P1.19, U1.4 (A2)
p0_b2_buff: Panel-1.7, U1.16 (B2)
p0_g1: P1.13, U1.9 (A7)
p0_g1_buff: Panel-1.2, U1.11 (B7)
p0_g2: P1.21, U1.6 (A4)
p0_g2_buff: Panel-1.6, U1.14 (B4)
p0_r1: P1.23, U1.8 (A6)
p0_r1_buff: Panel-1.1, U1.12 (B6)
p0_r2: P1.24, U1.5 (A3)
p0_r2_buff: Panel-1.5, U1.15 (B3)
p1_b1: P1.31, U3.7 (A5)
p1_b1_buff: Panel-2.3, U3.13 (B5)
p1_b2: P1.38, U3.4 (A2)
p1_b2_buff: Panel-2.7, U3.16 (B2)
p1_g1: P1.29, U3.9 (A7)
p1_g1_buff: Panel-2.2, U3.11 (B7)
p1_g2: P1.33, U3.6 (A4)
p1_g2_buf: Panel-2.6, U3.14 (B4)
p1_r1: P1.32, U3.8 (A6)
p1_r1_buff: Panel-2.1, U3.12 (B6)
p1_r2: P1.35, U3.5 (A3)
p1_r2_buff: Panel-2.5, U3.15 (B3)
p2_b1: P1.5, U4.7 (A5)
p2_b1_buff: Panel-3.3, U4.13 (B5)
p2_b2: P1.40, U4.4 (A2)
p2_b2_buff: Panel-3.7, U4.16 (B2)
p2_g1: P1.3, U4.9 (A7)
p2_g1_buff: Panel-3.2, U4.11 (B7)
p2_g2: P1.36, U4.6 (A4)
p2_g2_buf: Panel-3.6, U4.14 (B4)
p2_r1: P1.8, U4.8 (A6)
p2_r1_buff: Panel-3.1, U4.12 (B6)
p2_r2: P1.37, U4.5 (A3)
p2_r2_buff: Panel-3.5, U4.15 (B3)
row_A: P1.15, U2.7 (A5)
row_A_buff: Panel-1.9, Panel-2.9, Panel-3.9, U2.13 (B5)
row_B: P1.16, U2.8 (A6)
row_B_buff: Panel-1.10, Panel-2.10, Panel-3.10, U2.12 (B6)
row_C: P1.18, U2.6 (A4)
row_C_buff: Panel-1.11, Panel-2.11, Panel-3.11, U2.14 (B4)
row_D: P1.22, U2.5 (A3)
row_D_buff: Panel-1.12, Panel-2.12, Panel-3.12, U2.15 (B3)
row_E: P1.10, P3.1, U2.2 (A0)
strobe: P1.7, U2.3 (A1), U2.4 (A2), U2.9 (A7)
strobe_buff_0: Panel-1.14, U2.11 (B7)
strobe_buff_1: Panel-2.14, U2.16 (B2)
strobe_buff_2: Panel-3.14, U2.17 (B1)

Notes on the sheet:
Pi Power 5V
C alt. footprint
Jumper for 1:32 multiplexing: Selection if E-Line on Pin 4 or 8 Otherwise: Ground (for non-1:32).

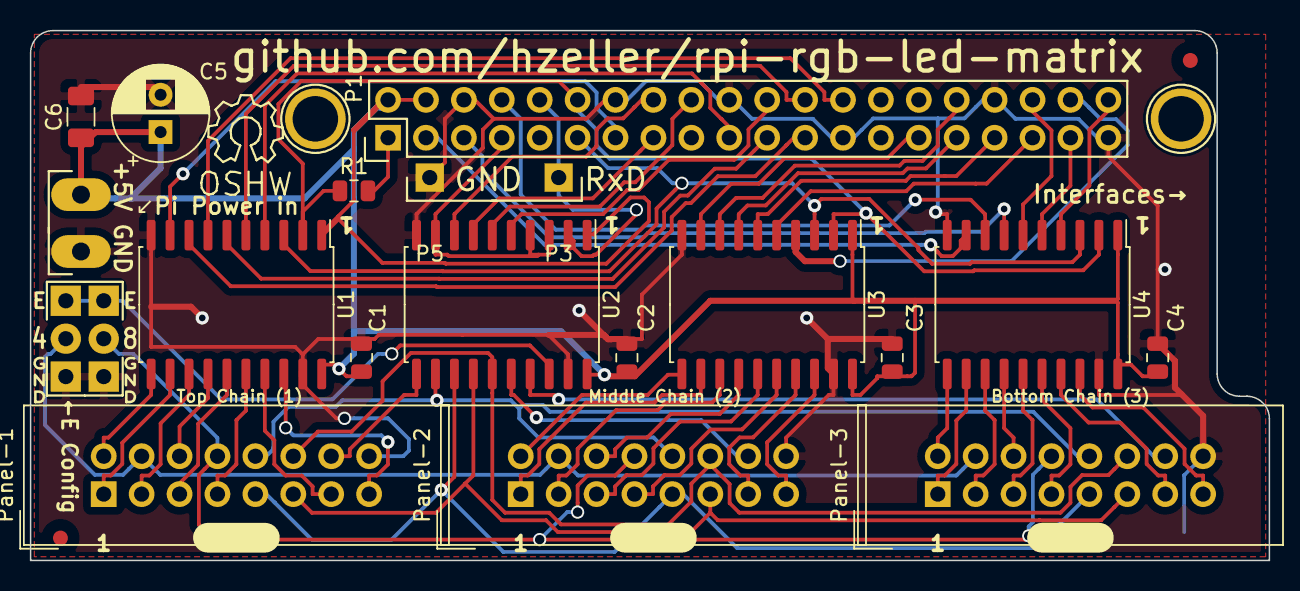
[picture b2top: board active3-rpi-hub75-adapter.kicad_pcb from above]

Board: 2 copper layers, 83.0 x 35.5 mm, 24 parts (0 on the bottom side), 63 nets.

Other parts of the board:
P20, P21: CONN_01X01; 1pin

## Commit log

2025-03-05 created readme
2025-03-05 added original repo reference to readme
2025-03-05 added utils gitignore
2025-03-05 created lib gitignore
2025-03-05 initialized led-matrix.h
2025-03-05 fleshed out canvas.h
2025-03-05 settings
2025-03-05 instantiated graphics header
2025-03-05 instantiated pixel mapper header
2025-03-05 instantiated thread header
2025-03-05 instantiated threaded-canvas-manipulator
2025-03-05 instantiated led matrix header
2025-03-07 created c-example
2025-03-07 initialized content-streamer
2025-03-11 settings and properties
2025-03-11 initialized led-matrix-c
2025-03-12 initialized MakeFile
2025-03-12 new setting maybe?
2025-03-12 initialized bdf-font.cc with errors
2025-03-12 initialized led-image-viewer.cc with errors
2025-03-12 initialized content-streamer.cc
2025-03-12 initialized Makefile in utils
2025-03-12 initialized README in utils
2025-03-20 created README for bindings
2025-03-20 added editor config
2025-03-20 added gitignore
2025-03-20 added Makefile
2025-03-20 added images
2025-03-22 more readme
2025-03-29 quick finish
2025-03-29 started bad sound interaction section of readme
2025-03-29 quick add
2025-04-29 finished README
2025-04-29 finished Bindings.cs
2025-04-29 initialized RGBLedMatrix.cs
2025-04-29 initialized RGBLedMatrixOptions.cs
2025-04-29 initialized csproj file
2025-05-02 initialized ScanModes.cs
2025-05-02 initialized Color.cs
2025-05-02 initialized Multiplexing.cs
2025-05-02 initialized RGBLedCanvas.cs
2025-05-02 Initialized RGBLedFont.cs
2025-05-02 Initialized InternalRGBLedMatrixOptions.cs
2025-05-02 added gitignore, MakeFile, and README for c# folder
2025-05-02 initialized c# font example
2025-05-02 initialized c# matrix rain example
2025-05-02 initialized c# minimal example
2025-05-02 initialized c# play gif example
2025-05-02 initialized c# pulsing brightness example
2025-05-08 created python README
2025-05-08 initialized totating 3D cube example
2025-05-09 python bindings gitignore, makefile, and readme
2025-05-09 python bindings rgbmatrix gitignore and makefile
2025-05-12 changed gitignore
2025-05-12 python bindings setup and rgbmatrix
2025-05-12 gif-viewer sample
2025-05-12 python graphics sample
2025-05-12 python samplebase
2025-05-12 grayscale block sample
2025-05-12 image draw sample
2025-05-12 image scroller sample
2025-05-12 image viewer sample
2025-05-13 pulsing brightness python sample
2025-05-13 pulsing colors python sample
2025-05-13 rotating block generator python sample
2025-05-13 runtext api use example
2025-05-14 simple square python sample
2025-05-14 run text python sample
2025-05-14 7x13.bdf font added
2025-05-14 example api use gitignore and makefile added
2025-05-14 example api use readme added
2025-05-16 c-example api use
2025-05-16 main demo example use
2025-05-16 image example use
2025-05-16 input example use
2025-05-16 ledcat example use
2025-05-19 added runtext16.ppm
2025-05-19 added clock example api use
2025-05-19 added minimal-example api use
2025-05-19 added pixel-mover example api use
2025-05-19 added scrolling-text example api-use
2025-05-19 added text-example api use
2025-05-19 image added
2025-05-19 adapter readme
2025-05-23 adapter active-3 makefile
2025-05-23 active-3 adapter readme
2025-05-23 adapter active3 rpi cache lib file
2025-05-27 active-3 adapter
2025-05-27 adapter kicad-scripts
2025-05-27 passive-3 adapter
2025-05-27 passive-rpi1 adapter
2025-05-27 adapter images
2025-05-29 framebuffer-internal
2025-05-30 framebuffer
